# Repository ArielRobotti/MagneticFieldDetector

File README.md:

# Magnetic Field Polarity Detector 
## This device is designed for use in the field of magical arts.

## Description
The Magnetic Field Polarity Detector is a compact device designed to detect the presence of a magnetic field and indicate its polarity through vibrations. When the device is exposed to a north-to-south magnetic field, it will vibrate intermittently, while a south-to-north magnetic field will cause continuous vibrations.

## Schematic Design and Simulation in Multisim 14
The chosen design is based on the implementation of a linear Hall sensor, AH49E, which provides an output voltage proportional to the intensity of the magnetic field. The sensor outputs a voltage within specific thresholds depending on the magnetic field intensity. This voltage is then processed by comparators to activate the vibration motor accordingly.

### Design Adaptations
To accommodate the power supply requirements of the circuit components, an additional boost converter stage was included. This stage provides a stable 5V output from the 3V battery. The motor is directly powered from the 3V line to prevent feedback into the 5V line.

## Usage
1. Ensure that the device is turned off before use.
2. Insert a 3V battery into the battery holder.
3. Turn on the device using the power switch.
4. Hold the Magnetic Field Polarity Detector near the target area.
5. Observe the vibration patterns:
- Intermittent vibrations indicate the presence of a magnetic field in the south-to-north direction.
- Continuous vibrations indicate the presence of a magnetic field in the north-to-south direction.
6. Move the detector away from the proximity of the magnetic object to stop the vibrations.
7. Turn off the device when not in use to conserve battery life.
  
## Specifications
- Dimensions: 25mm x 30mm
- Power Supply: 3V battery (included)
- Power Switch: On/Off control

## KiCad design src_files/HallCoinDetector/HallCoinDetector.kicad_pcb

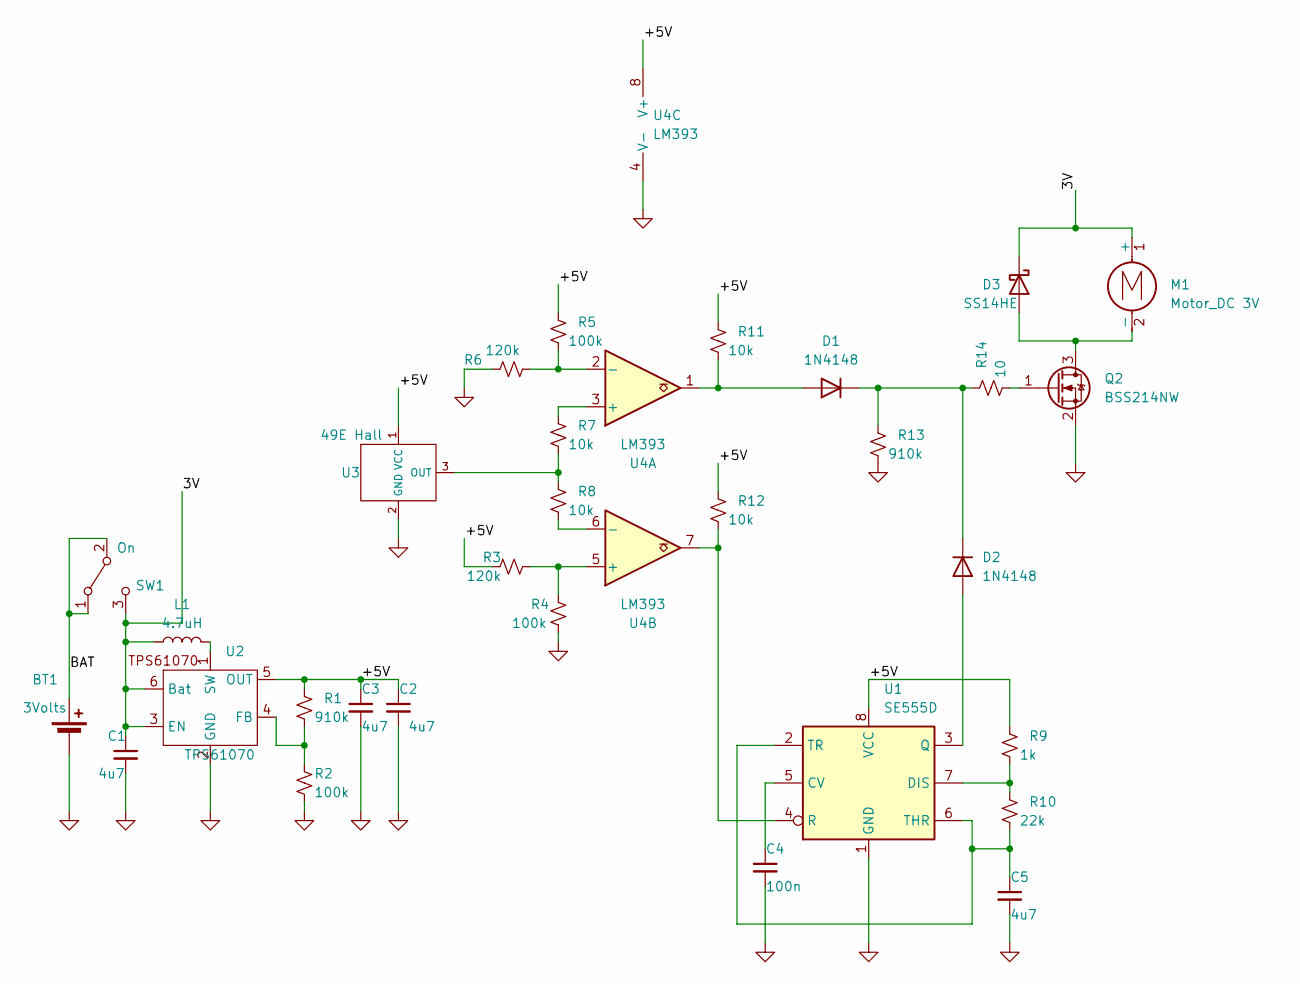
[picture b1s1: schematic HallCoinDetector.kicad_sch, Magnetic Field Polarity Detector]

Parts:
BT1: 3Volts; cr1616
C1, C2, C3, C5: 4u7; C_0805_2012Metric
C4: 100n; C_0603_1608Metric
D1, D2: 1N4148; D_SOD-123
D3: SS14HE; D_PowerDI-123
L1: 4.7uH; L_Wuerth_WE-TPC-3816
M1: Motor_DC 3V; PinHeader_1x02_P1.27mm_Vertical
Q2: BSS214NW; SOT-323_SC-70
R1, R13: 910k; R_0805_2012Metric
R2, R4, R5: 100k; R_0805_2012Metric
R3, R6: 120k; R_0805_2012Metric
R7, R8, R11, R12: 10k; R_0805_2012Metric
R9: 1k; R_0805_2012Metric
R10: 22k; R_0805_2012Metric
R14: 10; R_0805_2012Metric
SW1: On; SW_SPDT_PCM12
U1: SE555D; SOIC-8_3.9x4.9mm_P1.27mm
U2: TPS61070; SOT-23-6
U3: 49E Hall; SOT-23-3
U4: LM393; SOIC-8_3.9x4.9mm_P1.27mm

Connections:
/3V: C1.1, D3.1 (K), L1.1, M1.1 (+), SW1.3 (C), U2.3 (EN), U2.6 (Bat)
/+5V: C2.1, C3.1, R1.1, R3.1, R5.1, R9.1, R11.1, R12.1, U1.8 (VCC), U2.5 (OUT), U3.1 (VCC), U4.8 (V+)
/BAT: BT1.1 (+), SW1.1 (A), SW1.2 (B)
GND: BT1.2 (-), C1.2, C2.2, C3.2, C4.2, C5.2, Q2.2 (S), R2.2, R4.2, R6.1, R13.2, U1.1 (GND), U2.2 (GND), U3.2 (GND), U4.4 (V-)
unnamed: D1.2 (A), R11.2, U4.1
unnamed: D1.1 (K), D2.1 (K), R13.1, R14.1
unnamed: D2.2 (A), U1.3 (Q)
unnamed: D3.2 (A), M1.2 (-), Q2.3 (D)
unnamed: Q2.1 (G), R14.2
unnamed: C4.1, U1.5 (CV)
unnamed: R9.2, R10.1, U1.7 (DIS)
unnamed: R12.2, U1.4 (R), U4.7
unnamed: C5.1, R10.2, U1.2 (TR), U1.6 (THR)
unnamed: R1.2, R2.1, U2.4 (FB)
unnamed: L1.2, U2.1 (SW)
unnamed: R7.2, R8.1, U3.3 (OUT)
unnamed: R7.1, U4.3 (+)
unnamed: R5.2, R6.2, U4.2 (-)
unnamed: R3.2, R4.1, U4.5 (+)
unnamed: R8.2, U4.6 (-)

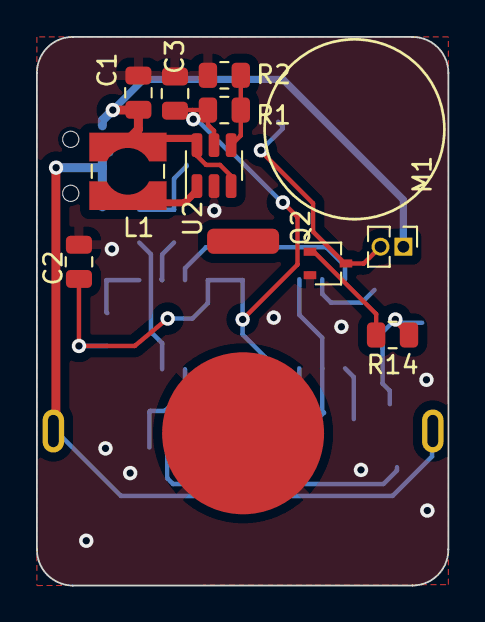
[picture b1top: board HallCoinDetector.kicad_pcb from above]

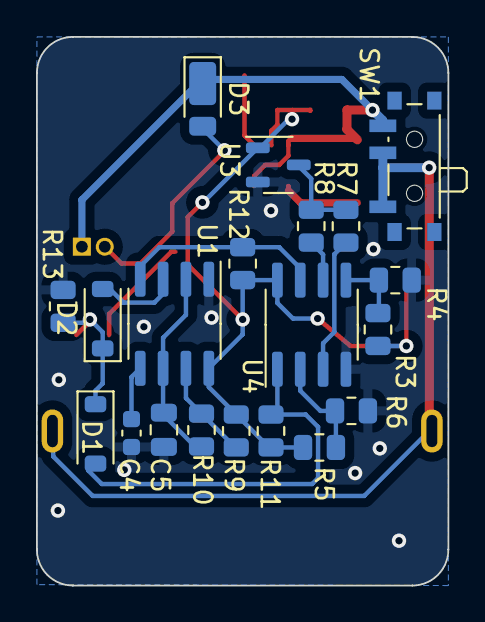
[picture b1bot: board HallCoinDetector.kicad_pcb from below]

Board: 2 copper layers, 22.9 x 30.5 mm, 31 parts (20 on the bottom side), 20 nets.

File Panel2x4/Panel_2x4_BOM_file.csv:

Comment,Designator,Footprint,LCSC Part Number
3Volts,BT1,Batery Holder:cr1616,
Motor_DC,M1,,C2685990
4u7,C1,C0805,C2835535
4u7,C2,C0805,C2835535
4u7,C3,C0805,C2835535
4u7,C5,C0805,C2835535
100n,C4,0603,C342854
1N4148,D1,SOD-123,C917030
1N4148,D2,SOD-123,C917030
SS14HE,D3,SOD-123HE,C4749020
4.7uH,L1,SMD,4x4mm,C5120868
BSS214NW,Q2,SOT-323,C3247496
910k,R1,R0805,C3016845
910k,R13,R0805,C3016845
100K,R2,R0805,C3017875
120k,R3,R0805,C268319
120k,R6,R0805,C268319
100k,R4,R0805,C3017875
100k,R5,R0805,C3017875
10k,R7,R0805,C3016734
10k,R8,R0805,C3016734
10k,R11,R0805,C3016734
10k,R12,R0805,C3016734
1k,R9,R0805,C3017842
22k,R10,R0805,C2889807
10,R14,R0805,C101420
On,SW1,SW_SPDT_PCM12,C493292
SE555D,U1,SO:SOIC-8,C7593
TPS61070,U2,SOT-23-6,C9841
49E Hall,U3,SOT-23,C85573
LM393,U4,SO:SOIC-8,C2931601

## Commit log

2023-06-25 Create README.md
    Readme
2023-06-25 Update README.md
    Fix
2023-06-28 diseño de librerias y ubicación de componentes
2023-06-29 first_delivery
2023-06-29 samples
2023-06-29 Gerber files
2023-07-26 panelizado
